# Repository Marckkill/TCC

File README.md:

# TCC - Sistema de Controle de Motor Trifásico com ESP32

Este repositório contém o projeto de TCC (Trabalho de Conclusão de Curso) que implementa um sistema de controle de motor trifásico utilizando ESP32 com modulação SPWM (Sinusoidal Pulse Width Modulation).

## 📋 Sobre o Projeto

O sistema desenvolvido é um inversor trifásico baseado no microcontrolador ESP32-S3, capaz de gerar sinais SPWM para acionamento de motores AC trifásicos. O projeto inclui monitoramento em tempo real de corrente e tensão, além de sistemas de proteção e segurança.

### Características Principais

- **Controle SPWM**: Modulação senoidal PWM trifásica com frequência configurável
- **Monitoramento em Tempo Real**: Leitura contínua de tensão e corrente RMS
- **Sistema de Proteção**: Detecção de sobrecorrente, sobretensão e falhas do sistema
- **Interface Serial**: Controle e monitoramento via comandos seriais
- **Hardware Personalizado**: PCB desenvolvida especificamente para o projeto

## 📁 Estrutura do Projeto

```
TCC/
├── 📄 Esquemáticos KiCad
│   ├── TCC.kicad_sch           # Esquemático principal
│   ├── filtro.kicad_sch        # Circuito de filtros
│   ├── fonte.kicad_sch         # Sistema de alimentação
│   ├── mcu.kicad_sch           # Microcontrolador ESP32
│   ├── sdf.kicad_sch           # Sistema de detecção de falhas
│   └── smp.kicad_sch           # Sistema de medição de potência
│
├── 🔧 Hardware
│   ├── TCC.kicad_pcb           # Layout da PCB
│   ├── TCC.kicad_pro           # Projeto KiCad
│   └── Componentes_Custom/     # Componentes personalizados
│       ├── ESP32/              # Footprint ESP32-S3
│       ├── FSBB30CH60/         # Módulo de potência
│       └── PJ320A/             # Conector de áudio
│
├── 💻 Firmware
│   └── Firmware.ino            # Código principal do ESP32
│
├── 📚 Documentação
│   ├── TCC.pdf                 # Documentação completa
│   ├── TCC-Fonte.pdf           # Esquemático da fonte
│   ├── TCC-MCU.pdf             # Esquemático do MCU
│   └── TCC-SMP.pdf             # Sistema de medição
│
└── 🔄 Backups
    └── TCC-backups/            # Backups automáticos do projeto
```

## 🔧 Hardware

### Componentes Principais

| Componente               | Modelo/Tipo | Função                         |
| ------------------------ | ----------- | ------------------------------ |
| **Microcontrolador**     | ESP32-S3    | Controle principal do sistema  |
| **Módulo de Potência**   | FSBB30CH60C | Inversor trifásico de potência |
| **Sensores de Corrente** | SCT013 (6x) | Monitoramento de corrente AC   |
| **Sensores de Tensão**   | ZMPT (3x)   | Monitoramento de tensão AC     |
| **Conector**             | PJ320A      | Interface de entrada de áudio  |

### Especificações Técnicas

- **Tensão de Entrada**: Barramento DC variável
- **Frequência de Saída**: 50 Hz (configurável)
- **Frequência PWM**: 10 kHz
- **Corrente Máxima**: 5A por fase (com proteção)
- **Tempo Morto**: 2μs entre chaves complementares
- **Taxa de Amostragem ADC**: 20 kHz

### Pinagem do ESP32-S3

#### Sinais PWM

```
Fase U: GPIO 18 (Alto), GPIO 35 (Baixo)
Fase V: GPIO 13 (Alto), GPIO 21 (Baixo)
Fase W: GPIO 14 (Alto), GPIO 17 (Baixo)
```

#### Sensores de Corrente (ADC1)

```
U_IN:  GPIO 1  (ADC1_CH0)    U_OUT: GPIO 2  (ADC1_CH1)
V_IN:  GPIO 3  (ADC1_CH2)    V_OUT: GPIO 4  (ADC1_CH3)
W_IN:  GPIO 5  (ADC1_CH4)    W_OUT: GPIO 6  (ADC1_CH5)
```

#### Sensores de Tensão (ADC1)

```
Tensão U: GPIO 7  (ADC1_CH6)
Tensão V: GPIO 8  (ADC1_CH7)
Tensão W: GPIO 9  (ADC1_CH8)
Vbus:     GPIO 10 (ADC1_CH9)
```

#### Segurança

```
VFO (Status): GPIO 36 (INPUT_PULLUP)
```

## 💻 Firmware

### Funcionalidades Implementadas

#### 🌊 Geração SPWM

- Modulação senoidal PWM trifásica
- Defasagem de 120° entre fases
- Índice de modulação configurável (0.1 - 1.0)
- Atualização a 1 kHz para suavidade do sinal

#### 📊 Monitoramento em Tempo Real

- **ADC Contínuo com DMA**: 20 kHz de amostragem
- **Cálculo RMS**: Janela deslizante de 400 amostras (20ms)
- **Buffer Circular**: Armazenamento eficiente de dados
- **Multitarefa**: Processamento paralelo com FreeRTOS

#### 🛡️ Sistema de Proteção

- **Sobrecorrente**: Trip em >5A por fase
- **Sobretensão**: Monitoramento do barramento DC
- **Status VFO**: Verificação do módulo de potência
- **Parada de Emergência**: Desabilitação imediata em falhas

#### 📡 Interface Serial

Comandos disponíveis:

```
start              - Iniciar o inversor
stop               - Parar o inversor
status             - Mostrar status do sistema
sensors            - Mostrar leituras dos sensores
reset              - Limpar falhas do sistema
set_mod <valor>    - Definir índice de modulação (0.1-1.0)
help               - Mostrar ajuda
```

### Principais Funções do Código

| Função                        | Descrição                              |
| ----------------------------- | -------------------------------------- |
| `setup_mcpwm()`               | Configuração do módulo MCPWM para SPWM |
| `setup_adc_continuous()`      | Inicialização do ADC contínuo com DMA  |
| `update_spwm()`               | Atualização dos duty cycles senoidais  |
| `calculate_rms_from_buffer()` | Cálculo RMS das amostras               |
| `check_safety_conditions()`   | Verificação das condições de segurança |
| `emergency_stop()`            | Parada de emergência do sistema        |

## 🚀 Como Usar

### Pré-requisitos

#### Software

- [Arduino IDE](https://www.arduino.cc/en/software) 2.0+
- [KiCad](https://www.kicad.org/) 7.0+ (para visualizar esquemáticos)
- Bibliotecas ESP32 (esp32 by Espressif Systems)

#### Hardware

- ESP32-S3 Development Board
- Módulo FSBB30CH60C
- Sensores SCT013 e ZMPT
- Fonte de alimentação adequada

### Instalação e Configuração

1. **Clone o repositório**:

   ```bash
   git clone https://github.com/usuario/TCC.git
   cd TCC
   ```

2. **Configure o Arduino IDE**:

   - Instale o pacote ESP32
   - Selecione "ESP32S3 Dev Module"
   - Configure a porta serial correta

3. **Compile e envie o firmware**:
   - Abra `Firmware/Firmware.ino`
   - Compile (Ctrl+R)
   - Envie para o ESP32 (Ctrl+U)

### Operação do Sistema

1. **Inicialização**:

   ```
   Sistema inicializado - Pronto para operação
   Comandos: start, stop, status, sensors, reset, set_mod <0.1-1.0>
   AVISO: Verifique todos os sistemas de segurança antes de iniciar!
   ```

2. **Verificar sensores**:

   ```
   sensors
   ```

3. **Iniciar o inversor**:

   ```
   start
   ```

4. **Monitorar operação**:
   ```
   status
   ```

### Exemplo de Uso

```bash
# Monitor serial a 115200 baud
sensors          # Verificar leituras
set_mod 0.5      # Configurar índice de modulação para 50%
start            # Iniciar operação
status           # Verificar status
stop             # Parar operação
```

## 📊 Monitoramento

### Dados Disponíveis

O sistema monitora continuamente:

- **Correntes RMS**: 6 canais (entrada e saída por fase)
- **Tensões RMS**: 3 fases + barramento DC
- **Status de Segurança**: VFO, sobrecorrente, sobretensão
- **Parâmetros SPWM**: Ângulo atual, índice de modulação

### Exemplo de Saída do Monitor

```
=== LEITURAS DOS SENSORES ===
Correntes (A):
  U_IN: 2.34  U_OUT: 2.31
  V_IN: 2.35  V_OUT: 2.33
  W_IN: 2.36  W_OUT: 2.34
Tensões (V):
  U: 230.1  V: 229.8  W: 230.3
Tensão Vbus: 325.4 V
Status VFO: OK
Índice de Modulação: 0.800
=============================
```

## 🛡️ Segurança

### Sistemas de Proteção Implementados

1. **Sobrecorrente**: Monitoramento contínuo com trip em 5A
2. **Sobretensão**: Proteção do barramento DC
3. **VFO**: Monitoramento do status do módulo de potência
4. **Tempo Morto**: Prevenção de curto-circuito entre chaves

### ⚠️ Avisos de Segurança

- **ALTA TENSÃO**: Este projeto trabalha com tensões perigosas
- **Sempre desligue a alimentação** antes de fazer conexões
- **Verifique todas as conexões** antes de energizar
- **Use EPIs adequados** durante testes
- **Tenha um sistema de parada de emergência** sempre acessível

## 🔄 Desenvolvimento

### Estrutura do Código

```cpp
// Configurações principais
#define PWM_FREQUENCY 10000        // 10 kHz
#define MODULATION_FREQUENCY 50    // 50 Hz
#define ADC_SAMPLE_FREQ_HZ 20000   // 20 kHz
#define MAX_CURRENT_AMPS 5.0       // 5A máximo

// Loop principal
void loop() {
    update_spwm();              // Atualiza SPWM (1 kHz)
    update_sensors();           // Lê sensores (100 Hz)
    check_safety_conditions();  // Verifica segurança
    process_serial_commands();  // Processa comandos
}
```

### Tecnologias Utilizadas

- **ESP-IDF**: Framework nativo do ESP32
- **FreeRTOS**: Sistema operacional em tempo real
- **MCPWM**: Módulo PWM dedicado do ESP32
- **ADC Contínuo**: Amostragem de alta velocidade com DMA
- **KiCad**: Design de circuitos e PCB

## 📈 Melhorias Futuras

- [ ] Controle de velocidade com feedback
- [ ] Interface web para controle remoto
- [ ] Controle de torque
- [ ] Algoritmos de controle avançados (FOC)
- [ ] Análise de espectro harmônico
- [ ] Comunicação CAN/Modbus
- [ ] Sistema de logs em cartão SD

## 📄 Documentação

### Arquivos de Documentação

- **[TCC.pdf](TCC.pdf)**: Documentação completa do projeto
- **[TCC-Fonte.pdf](TCC-Fonte.pdf)**: Detalhes do sistema de alimentação
- **[TCC-MCU.pdf](TCC-MCU.pdf)**: Circuito do microcontrolador
- **[TCC-SMP.pdf](TCC-SMP.pdf)**: Sistema de medição de potência

### Referências Técnicas

- [ESP32-S3 Technical Reference Manual](https://www.espressif.com/sites/default/files/documentation/esp32-s3_technical_reference_manual_en.pdf)
- [FSBB30CH60C Datasheet](https://www.onsemi.com/pdf/datasheet/fsbb30ch60c-d.pdf)
- Normas de segurança para inversores de frequência

## 👨‍💻 Autor

**José Fonseca**

- Projeto de TCC - Engenharia Eletrônica

## 📝 Licença

Este projeto foi desenvolvido como Trabalho de Conclusão de Curso (TCC) e está disponível para fins educacionais e de pesquisa.

---

## 🆘 Suporte

Para dúvidas ou problemas:

1. Verifique a documentação técnica incluída
2. Consulte os comentários no código fonte
3. Revise as configurações de hardware
4. Verifique as conexões elétricas

**⚠️ LEMBRE-SE: Segurança sempre em primeiro lugar ao trabalhar com sistemas de potência!**

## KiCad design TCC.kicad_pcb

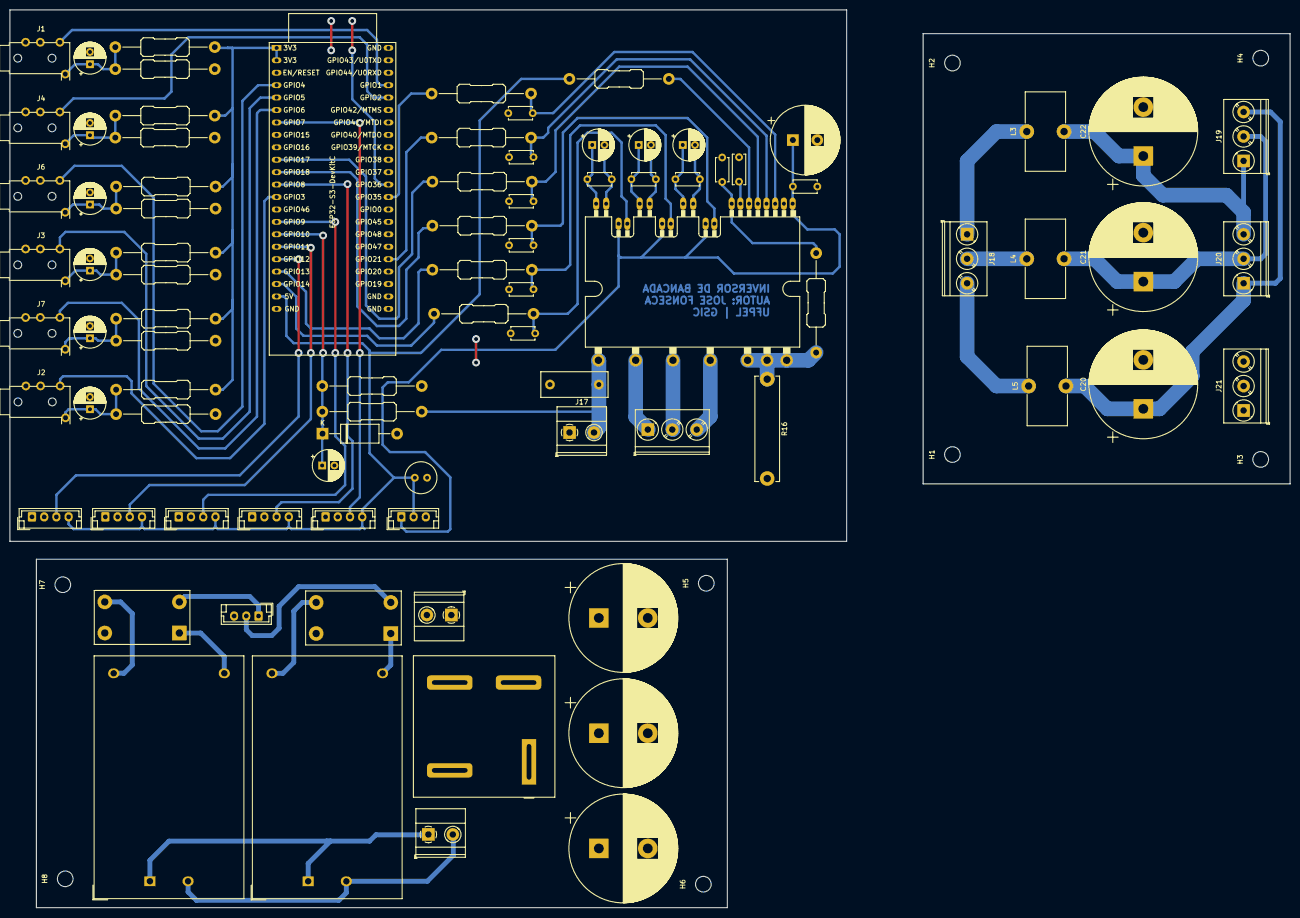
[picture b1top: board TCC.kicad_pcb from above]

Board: 2 copper layers, 261.6 x 183.5 mm, 94 parts (0 on the bottom side), 54 nets.

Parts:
C1, C2, C3, C20, C21, C22: 100u/500V; CP_Radial_D22.0mm_P10.00mm_SnapIn
C4, C5, C6, C8, C9, C10: 1n; C_Disc_D4.7mm_W2.5mm_P5.00mm
C7: 10u; C_Radial_D6.3mm_H5.0mm_P2.50mm
C11, C12, C13: 22u; CP_Radial_D6.3mm_P2.50mm
C14: 33n; C_Disc_D6.0mm_W2.5mm_P5.00mm
C15, C16, C17: 100n; C_Disc_D4.7mm_W2.5mm_P5.00mm
C18: 1000u; CP_Radial_D14.0mm_P5.00mm
C19: 1u; C_Disc_D4.7mm_W2.5mm_P5.00mm
C23: 10n; C_Disc_D4.7mm_W2.5mm_P5.00mm
C24: 0.22u/400v; C_Rect_L13.5mm_W5.0mm_P10.00mm_FKS3_FKP3_MKS4
C25, C26, C27, C28, C29, C30, C31: 10u; CP_Radial_D6.3mm_P2.50mm
D1: KBPC5010T; Diode_Bridge_DIGITRON_KBPC_T
DZ1: 3v3; D_DO-15_P15.24mm_Horizontal
H1, H2, H3, H4, H5, H6, H7, H8: MountingHole_M3; MountingHole_3.2mm_M3
IC1: FSBB30CH60
J1, J2, J3, J4, J6, J7: AudioJack2; Jack_3.5mm_KoreanHropartsElec_PJ-320D-4A_Horizontal
J5, J14, J17: Screw_Terminal_01x02; TerminalBlock_Phoenix_MKDS-1,5-2_1x02_P5.00mm_Horizontal
J8, J18, J19, J20, J21: Screw_Terminal_3_P5.00mm; TerminalBlock_Phoenix_PT-1,5-3-5.0-H_1x03_P5.00mm_Horizontal
J9, J10, J11, J12, J13: JST_04; JST_EH_B4B-EH-A_1x04_P2.50mm_Vertical
J15, J16: JST_03; JST_EH_B3B-EH-A_1x03_P2.50mm_Vertical
L1, L2: Choke; L_CommonMode_Toroid_Vertical_L19.3mm_W10.8mm_Px6.35mm_Py15.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
L3, L4, L5: 220uH; L_Toroid_Vertical_L16.0mm_W8.0mm_P7.62mm
PS1: HLK-10M05; Converter_ACDC_Hi-Link_HLK-10Mxx
PS2: HLK-10M15; Converter_ACDC_Hi-Link_HLK-10Mxx
R1, R2, R3, R4, R5, R6, R13: 100; R_Axial_DIN0411_L9.9mm_D3.6mm_P20.32mm_Horizontal
R7, R8, R18, R19, R20, R21, R22, R23, R24, R25, R26, R27, R29: 10k; R_Axial_DIN0411_L9.9mm_D3.6mm_P20.32mm_Horizontal
R12: 4k7; R_Axial_DIN0411_L9.9mm_D3.6mm_P20.32mm_Horizontal
R16: 11m; R_Bare_Metal_Element_L21.3mm_W4.8mm_P20.30mm
R28: 1M; R_Axial_DIN0411_L9.9mm_D3.6mm_P20.32mm_Horizontal
U1: ESP32-S3-DevKitC

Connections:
+3.3V: R7.1, R8.1, R18.1, R22.1, R23.1, R24.1, U1.1 (3V3), U1.2 (3V3)
+5V: C7.1, J9.4, J10.4, J11.4, J12.4, J13.4, J15.2, J16.2, L1.2, R12.1, U1.21 (5V)
+15V: C18.1, C19.1, IC1.1 (VCCL), IC1.10 (VCCUH), IC1.14 (VCCVH), IC1.18 (VCCWH), J15.1, J16.1, L2.2
AmpSens_L1_AF: J1.T, U1.41 (GPIO1/ADC1_CH0)
AmpSens_L1_DF: J4.T, U1.40 (GPIO2/ADC1_CH1)
AmpSens_L2_AF: J2.T, U1.13 (GPIO3/ADC1_CH2)
AmpSens_L2_DF: J6.T, U1.4 (GPIO4/ADC1_CH3)
AmpSens_L3_AF: J3.T, U1.5 (GPIO5/ADC1_CH4)
AmpSens_L3_DF: J7.T, U1.6 (GPIO6/ADC1_CH5)
CSC: C23.1, IC1.8 (CSC), R13.1
GND: C1.2, C2.2, C3.2, C4.2, C5.2, C6.2, C7.2, C8.2, C9.2, C10.2, C14.2, C18.2, C19.2, C20.2, C21.2, C22.2, C23.2, C24.2, C25.2, C26.2, C27.2, C28.2, C29.2, C30.2, C31.2, D1.3 (-), DZ1.2 (A), IC1.2 (COM), J9.1, J9.2, J10.1, J10.2, J11.1, J11.2, J12.1, J12.2, J13.1, J13.2, J14.2, J15.3, J16.3, J17.1, J21.1, J21.2, J21.3, L1.4, L2.4, R16.2, R19.2, R20.2, R21.2, R25.2, R26.2, R27.2, R29.2, U1.22 (GND), U1.23 (GND), U1.24 (GND), U1.44 (GND)
INUH: C8.1, IC1.9 (INUH), R4.2
INUL: C10.1, IC1.3 (INUL), R6.2
INVH: C4.1, IC1.13 (INVH), R1.2
INVL: C9.1, IC1.4 (INVL), R5.2
INWH: C5.1, IC1.17 (INWH), R2.2
INWL: C6.1, IC1.5 (INWL), R3.2
unnamed: C20.1, J19.3, J20.1, L5.2
unnamed: C21.1, J19.2, J20.2, L4.2
unnamed: C22.1, J19.1, J20.3, L3.2
unnamed: C25.1, J1.S, R7.2, R19.1
unnamed: C26.1, J2.S, R8.2, R20.1
unnamed: C27.1, J3.S, R18.2, R21.1
unnamed: C28.1, J4.S, R22.2, R25.1
unnamed: C29.1, J6.S, R23.2, R26.1
unnamed: C30.1, J7.S, R24.2, R27.1
unnamed: C14.1, IC1.7 (CFOD)
unnamed: IC1.21 (NU), IC1.22 (NV), IC1.23 (NW), R13.2, R16.1
unnamed: IC1.24 (U), J8.3
unnamed: IC1.25 (V), J8.2
unnamed: C11.2, C15.2, IC1.11 (VBU)
unnamed: C12.2, C16.2, IC1.15 (VBV)
unnamed: C13.2, C17.2, IC1.19 (VBW)
unnamed: C11.1, C15.1, IC1.12 (VSU)
unnamed: C12.1, C16.1, IC1.16 (VSV)
unnamed: C13.1, C17.1, IC1.20 (VSW)
unnamed: IC1.26 (W), J8.1
unnamed: J18.1, L3.1
unnamed: J18.2, L4.1
unnamed: J18.3, L5.1
PWM_UH: R4.1, U1.11 (GPIO18/ADC2_CH7)
PWM_UL: R6.1, U1.32 (GPIO35)
PWM_VH: R1.1, U1.19 (GPIO13/ADC2_CH2)
PWM_VL: R5.1, U1.27 (GPIO21)
PWM_WH: R2.1, U1.20 (GPIO14/ADC2_CH3)
PWM_WL: R3.1, U1.10 (GPIO17/ADC2_CH6)
VBUS: C1.1, C2.1, C3.1, C24.1, D1.1 (+), IC1.27, J14.1, J17.2, R28.1
VFO: IC1.6 (VFO), R12.2, U1.33 (GPIO36)
VoltSens_L1: J9.3, U1.7 (GPIO7/ADC1_CH6)
VoltSens_L2: J10.3, U1.12 (GPIO8/ADC1_CH7)
VoltSens_L3: J11.3, U1.15 (GPIO9/ADC1_CH8)
VoltSens_L12: J12.3, U1.17 (GPIO11/ADC2_CH0)
VoltSens_L23: J13.3, U1.18 (GPIO12/ADC2_CH1)
VoltSens_Link: C31.1, DZ1.1 (K), R28.2, R29.1, U1.16 (GPIO10/ADC1_CH9)

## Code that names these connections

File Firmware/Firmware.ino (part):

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 *  - Parar e falhar DESLIGAM AS SEIS CHAVES pelo "brake" do MCPWM (estágio de saída, depois
 *    do tempo morto). A v1 "parava" pondo 50% de razão cíclica: a ponte continuava chaveando,
 *    inclusive depois de uma falha, e já chaveava desde o boot, antes do "start".
 *  - O VFO do módulo derruba o PWM no HARDWARE (falha por GPIO do MCPWM), em nanossegundos.
 *  - Pré-carga dos capacitores de bootstrap antes de partir (chaves de baixo ligadas ~20 ms).
 *  - Rampa de frequência e V/f (com boost); frequência negativa inverte o sentido.
 *  - ADC: formato TYPE2 (o único que o ESP32-S3 aceita; com TYPE1 a v1 abortava no boot),
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#include "esp_adc/adc_cali_scheme.h"

// ============================ Pinos (esquemático V1) ============================
// ⚠️ GPIO35/36/37 são da PSRAM octal nos módulos N8R8/N16R8 (o YD-ESP32-S3 N16R8 é um
// deles). Nesses módulos, religue UL e VFO a pinos livres (ex.: 38 e 39) e troque aqui.
#define PIN_UH 18
#define PIN_UL 35
#define PIN_VH 13
#define PIN_VL 21
#define PIN_WH 14
#define PIN_WL 17
#define PIN_VFO 36 // ativo em nível BAIXO (open-collector do módulo)

// ============================ PWM ============================
#define PWM_RES_HZ 10000000                     // 10 MHz -> 0,1 us por tick
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#define RAMPA_PADRAO 10.0f // Hz/s

// ============================ Medidas ============================
// ADC1_CH0..CH9 = GPIO1..GPIO10, na ordem do esquemático. GPIO11/12 (L12/L23) são ADC2: fora.
#define N_CANAIS 10
#define ADC_TAXA_HZ 20000   // total -> 2 kHz por canal
#define JANELA 400          // amostras por canal = 200 ms (10 ciclos de 50 Hz)
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
// ============================ Proteções ============================
#define I_RMS_MAX 5.0f      // A rms, qualquer sensor (lento: janela de 200 ms)
#define I_PICO_MAX 12.0f    // A instantâneo (rápido: ~0,5 ms). O curto é com o CSC do módulo.
#define VBUS_MAX 360.0f     // V. O ADC satura perto de 375 V com este divisor.
#define VBUS_MIN 20.0f      // V, mínimo para partir
#define VBUS_FREIO 340.0f   // V: acima disso a desaceleração para (regeneração do motor)
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  ESP_ERROR_CHECK(mcpwm_new_soft_fault(&sfc, &falha_sw));
  mcpwm_gpio_fault_config_t gfc = {};
  gfc.group_id = 0;
  gfc.gpio_num = PIN_VFO;
  gfc.flags.active_level = 0;
  gfc.flags.pull_up = true;
  ESP_ERROR_CHECK(mcpwm_new_gpio_fault(&gfc, &falha_vfo));
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static void controle(float dt) {
  // Falhas
  if (estado == RODANDO || estado == PARANDO) {
    if (digitalRead(PIN_VFO) == LOW) disparar("VFO do modulo (curto no shunt ou subtensao 15 V)");
    for (int i = 0; i < 6; i++)
      if (medida[i] > I_RMS_MAX) disparar("sobrecorrente (rms)");
  }
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  const char *ESTADOS[] = {"PARADO", "RODANDO", "PARANDO", "FALHA"};
  Serial.printf("Estado %s | f %.2f Hz (alvo %.2f, rampa %.1f Hz/s) | m %.3f %s | VFO %s\n",
                ESTADOS[estado], freq, alvo, rampa, mod_q15 / 32767.0f, vf ? "(V/f)" : "(fixo)",
                digitalRead(PIN_VFO) ? "ok" : "FALHA");
  for (int i = 0; i < N_CANAIS; i++)
    Serial.printf("%s %.2f%s", NOME[i], medida[i], i < 6 ? " A  " : " V  ");
  Serial.println();
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  } else if (cmd == "mon" && !isnan(arg)) {
    mon_ms = (uint32_t)arg;
  } else if (cmd == "reset") {
    if (digitalRead(PIN_VFO) == LOW) Serial.println("VFO ainda em falha.");
    else {
      parar_agora();
      motivo = nullptr;
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
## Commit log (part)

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2025-02-24 Init
2025-03-16 midsave
2025-05-05 change conector
2025-06-18 final
2025-08-17 Firmware v1
2025-08-17 readme
